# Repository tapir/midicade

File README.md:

Midicade
--------

An ATMega32U4 based Midi Fighter clone

Dependencies
------------

* ezButton
* MIDIUSB
* FastLED
* LibPrintf (Used only in debug mode)

TODO
----

- Fixed: Bottom enclosure flex
- Fixed: Enclosure bototm/top mating tolerances
- Fixed: Small fixes to make it suitable for FDM printing
- Fixed: Reset circuit
- Find better rubber feet (too soft)
- Clean up software to bare minimum
- Document EEPROM structure and default values
- Document general hardware info
- Include STEP files and put a link to OnShape files
- Change to Sparkfun or Polulu bootloader to get rid of the 8 second boot delay

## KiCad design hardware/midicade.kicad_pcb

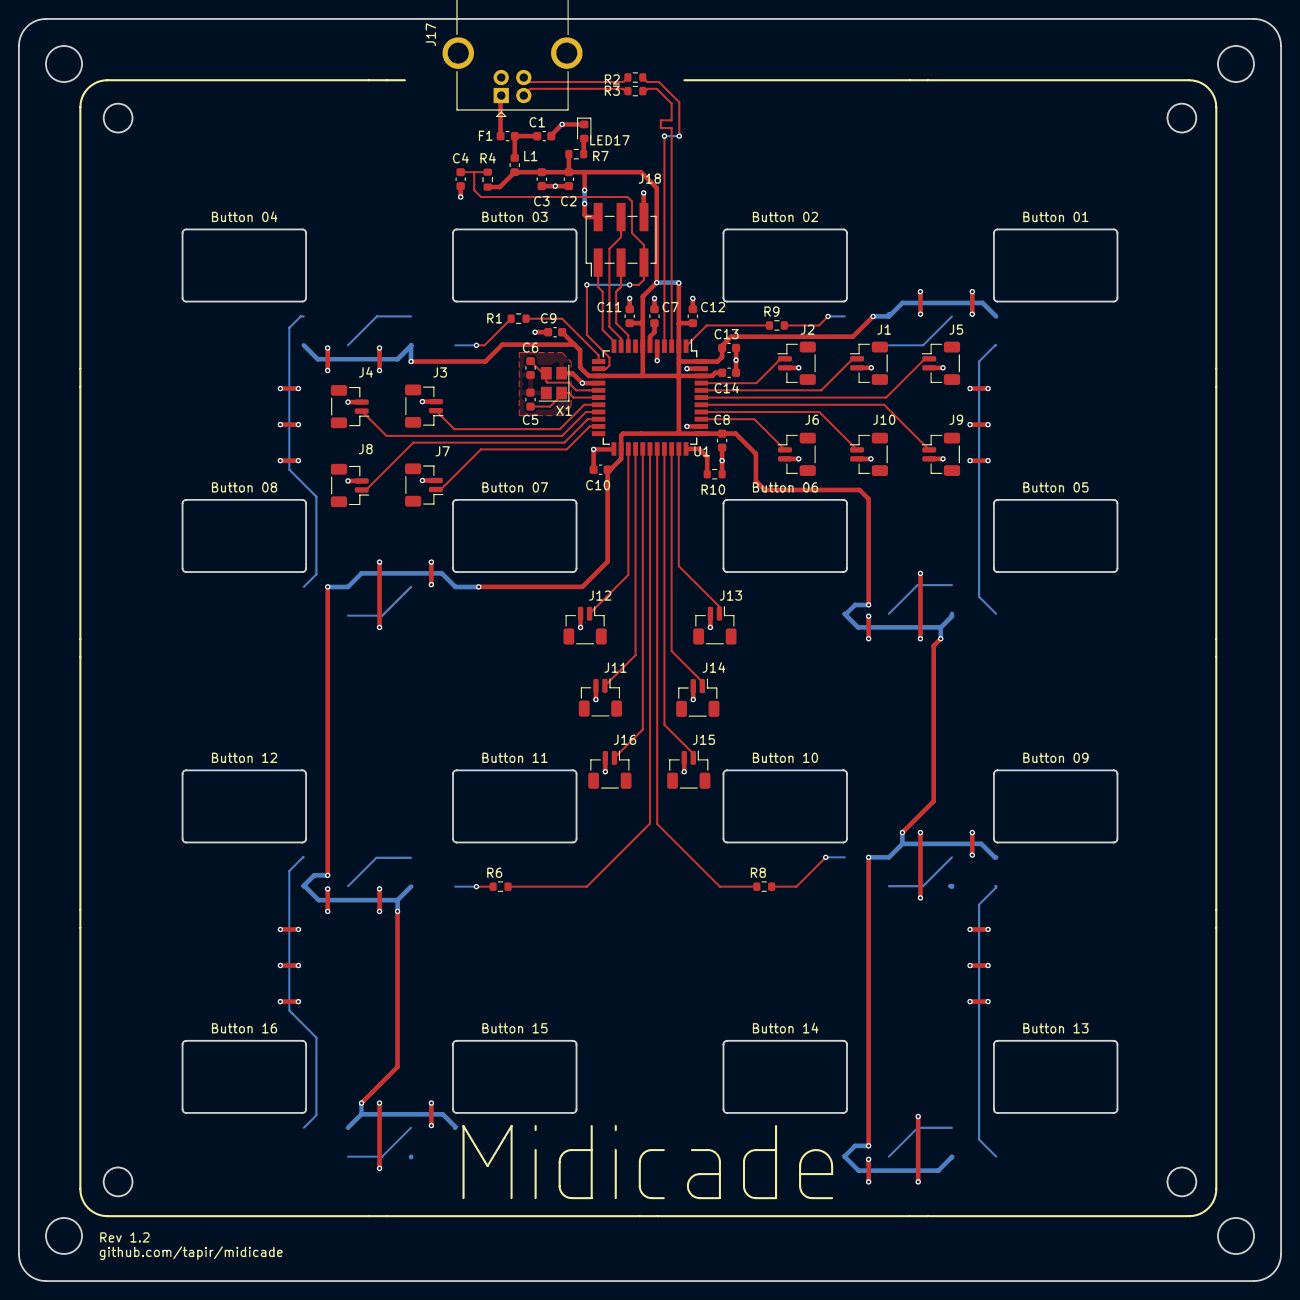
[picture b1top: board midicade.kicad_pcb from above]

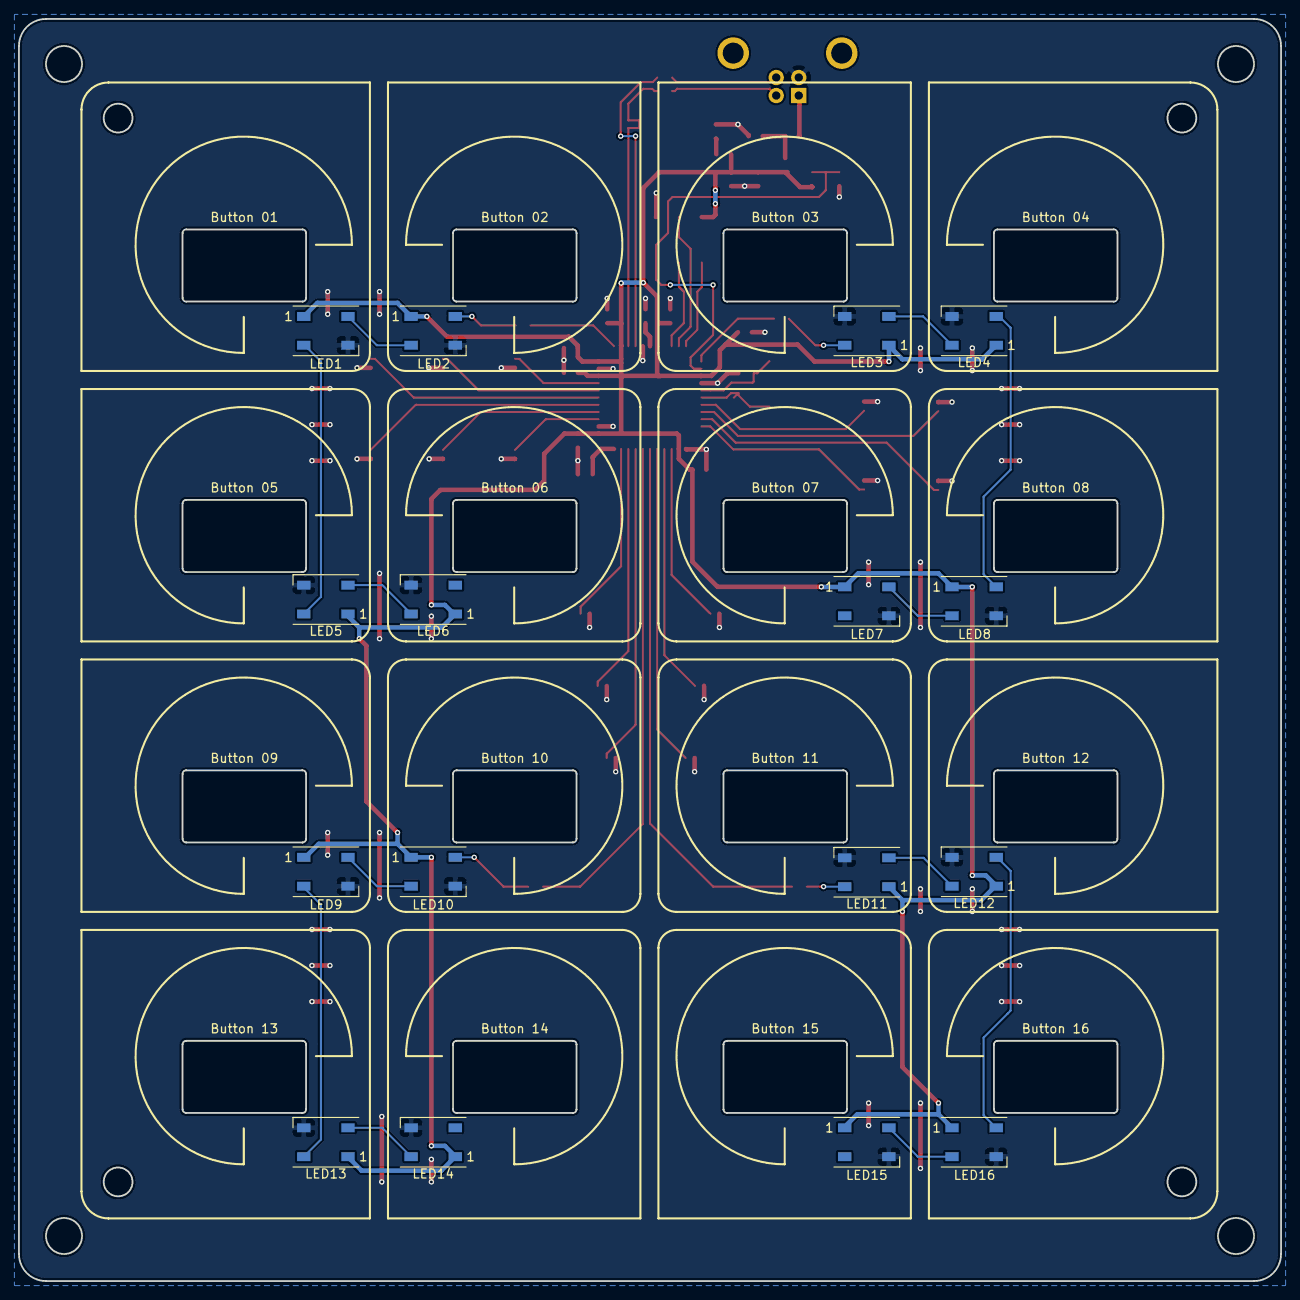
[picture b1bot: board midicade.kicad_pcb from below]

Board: 2 copper layers, 140.0 x 140.0 mm, 62 parts (16 on the bottom side), 53 nets.

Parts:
C1: 10nF; C_0603_1608Metric
C2, C4, C8, C9, C10, C11, C12, C13, C14: 100nF; C_0603_1608Metric
C3: 10uF; C_0603_1608Metric
C5, C6: 22pF; C_0603_1608Metric
C7: 1uF; C_0603_1608Metric
F1: 0603L050; Fuse_0603_1608Metric
J1, J2, J3, J4, J5, J6, J7, J8, J9, J10, J11, J12, J13, J14, J15, J16: Conn_01x02; JST_SH_BM02B-SRSS-TB_1x02-1MP_P1.00mm_Vertical_3D
J17: USB_B; USB_B_OST_USB-B1HSxx_Horizontal_3D
J18: Conn_01x06; PinHeader_2x03_P2.54mm_Vertical_SMD
L1: BLM18PG300SN1D; L_0603_1608Metric
LED1, LED2, LED3, LED4, LED5, LED6, LED7, LED8, LED9, LED10, LED11, LED12, LED13, LED14, LED15, LED16: WS2812B-V5; LED_WS2812B_PLCC4_5.0x5.0mm_P3.2mm
LED17: LED; LED_0603_1608Metric
R1, R6, R8, R9: 330; R_0603_1608Metric
R2, R3: 22; R_0603_1608Metric
R4, R10: 10K; R_0603_1608Metric
R7: 470; R_0603_1608Metric
U1: ATmega32U4; TQFP-44_10x10mm_P0.8mm
X1: ±10ppm 12pF; Crystal_SMD_3225-4Pin_3.2x2.5mm

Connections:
+5V: C2.1, C3.1, C8.1, C9.1, C10.1, C11.1, C12.1, C13.1, C14.1, J18.2, L1.2, LED1.1, LED2.1, LED3.1, LED4.1, LED5.1, LED6.1, LED7.1, LED8.1, LED9.1, LED10.1, LED11.1, LED12.1, LED13.1, LED14.1, LED15.1, LED16.1, R4.2, R7.1, U1.2, U1.7, U1.14, U1.24, U1.34, U1.42, U1.44
/D0: J8.1, U1.20
/D1: J7.1, U1.21
/D2: J4.1, U1.19
/D3: J3.1, U1.18
/D4: J12.1, U1.25
/D5: J14.1, U1.31
/D6: J16.1, U1.27
/D7: R9.2, U1.1
/D8: R6.2, U1.28
/D9: R8.2, U1.29
/D10: J15.1, U1.30
/D11: R1.2, U1.12
/D12: J11.1, U1.26
/D13: J13.1, U1.32
/D18: J6.1, U1.36
/D19: J10.1, U1.37
/D20: J9.1, U1.38
/D21: J5.1, U1.39
/D22: J1.1, U1.40
/D23: J2.1, U1.41
/DN: R3.1, U1.3
/DP: R2.2, U1.4
/MISO: J18.1, U1.11
/MOSI: J18.4, U1.10
/RESET: C4.1, J18.5, R4.1, U1.13
/SCK: J18.3, U1.9
GND: C1.2, C2.2, C3.2, C4.2, C5.2, C6.2, C7.2, C8.2, C9.2, C10.2, C11.2, C12.2, C13.2, C14.2, J1.2, J2.2, J3.2, J4.2, J5.2, J6.2, J7.2, J8.2, J9.2, J10.2, J11.2, J12.2, J13.2, J14.2, J15.2, J16.2, J17.4, J18.6, LED1.3, LED2.3, LED3.3, LED4.3, LED5.3, LED6.3, LED7.3, LED8.3, LED9.3, LED10.3, LED11.3, LED12.3, LED13.3, LED14.3, LED15.3, LED16.3, LED17.1, R10.1, U1.5, U1.15, U1.23, U1.35, U1.43, X1.2, X1.4
unnamed: C1.1, F1.2, L1.1
unnamed: C5.1, U1.17, X1.1
unnamed: C6.1, U1.16, X1.3
unnamed: C7.1, U1.6
unnamed: F1.1, J17.1
unnamed: J17.2, R3.2
unnamed: J17.3, R2.1
unnamed: LED1.2, LED5.4
unnamed: LED1.4, LED2.2
unnamed: LED2.4, R9.1
unnamed: LED3.2, LED4.4
unnamed: LED3.4, R1.1
unnamed: LED4.2, LED8.4
unnamed: LED5.2, LED6.4
unnamed: LED7.4, LED8.2
unnamed: LED9.4, LED10.2
unnamed: LED10.4, R8.1
unnamed: LED11.2, LED12.4
unnamed: LED11.4, R6.1
unnamed: LED12.2, LED16.4
unnamed: LED13.2, LED14.4
unnamed: LED9.2, LED13.4
unnamed: LED15.4, LED16.2
unnamed: LED17.2, R7.2
unnamed: R10.2, U1.33

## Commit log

2021-01-30 formatting
2021-02-15 initial hardware design
2021-02-15 minor production changes
2021-02-16 update LED resistor value
2021-03-20 ws2812b based software overhaul
2021-03-20 fixed pin naming to match leonardo
2021-03-20 arduino ide config files
2021-03-20 fix board manager file name
2021-03-20 fix arduino package structure
2021-03-20 bump version
2021-03-20 fix board group name
2021-03-20 try to fix category name again
2021-03-20 new version
2021-03-20 fix boards.txt
2021-03-20 fix usb vid pid
2021-03-20 orrect bootloader and vid pid names
2021-04-21 style and input buffer flush
2021-04-27 add todo
2021-04-27 rev 1.2 hardware
2021-04-27 bootloader todo
